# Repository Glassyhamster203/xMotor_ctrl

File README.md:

# xMotor_ctrl 

## An esp32 project

Project for HFUT RoboMaster team intramural competitions

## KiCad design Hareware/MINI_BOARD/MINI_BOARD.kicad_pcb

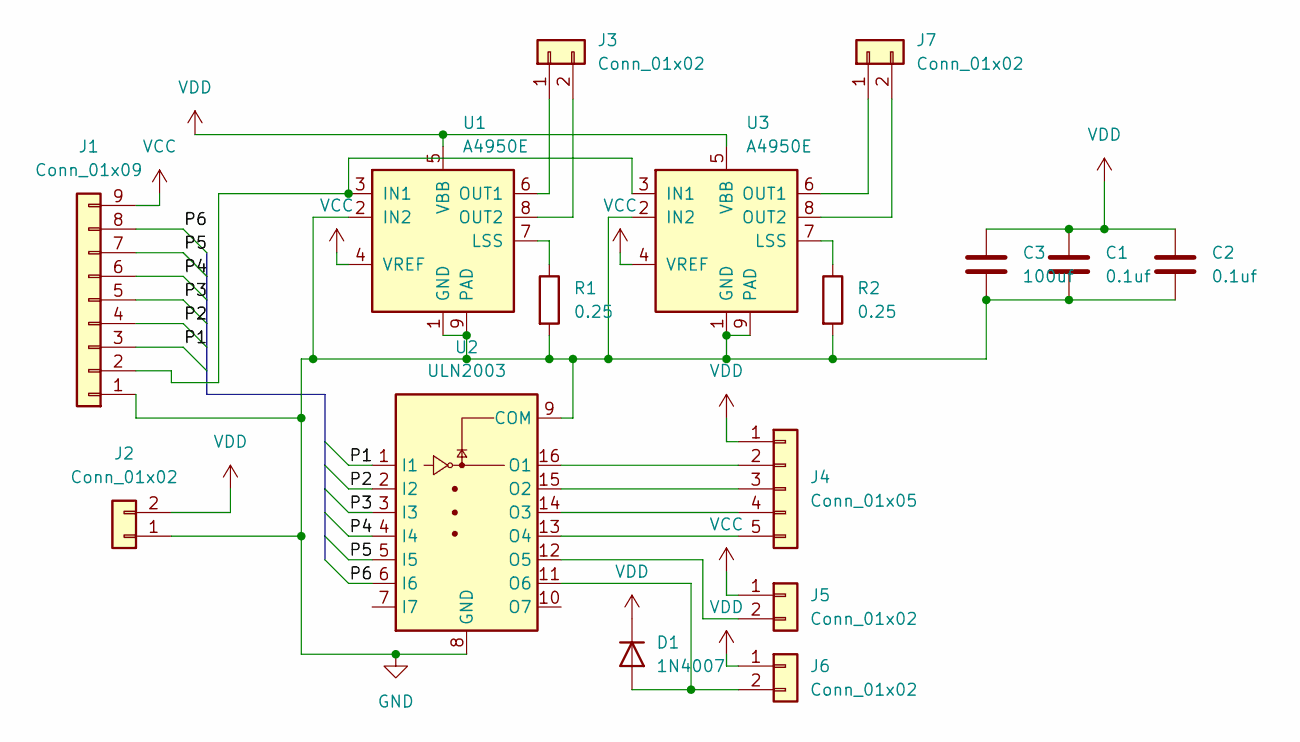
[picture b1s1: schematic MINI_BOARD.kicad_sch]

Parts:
C1, C2: 0.1uf; C_0603_1608Metric
C3: 100uf; CP_Radial_Tantal_D6.0mm_P5.00mm
D1: 1N4007; D_DO-41_SOD81_P10.16mm_Horizontal
J1: Conn_01x09; Wuerth_WR-WTB_64800911622_1x09_P1.50mm_Vertical
J2, J3, J6, J7: Conn_01x02; PhoenixContact_MCV_1,5_2-G-3.81_1x02_P3.81mm_Vertical
J4: Conn_01x05; PinHeader_1x05_P2.54mm_Vertical
J5: Conn_01x02; PinHeader_1x02_P2.54mm_Vertical
R1: 0.25; R_2512_6332Metric_Pad1.40x3.35mm_HandSolder
R2: 0.25; R_2816_7142Metric_Pad3.20x4.45mm_HandSolder
U1, U3: A4950E; SOIC-8-1EP_3.9x4.9mm_P1.27mm_EP2.41x3.3mm
U2: ULN2003; SOP-16_3.9x9.9mm_P1.27mm

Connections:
/P1: J1.3, U2.1 (I1)
/P2: J1.4, U2.2 (I2)
/P3: J1.5, U2.3 (I3)
/P4: J1.6, U2.4 (I4)
/P5: J1.7, U2.5 (I5)
/P6: J1.8, U2.6 (I6)
GND: C1.2, C2.2, C3.2, J1.1, J2.1, R1.2, R2.2, U1.1 (GND), U1.2 (IN2), U1.9 (PAD), U2.8 (GND), U2.9 (COM), U3.1 (GND), U3.2 (IN2), U3.9 (PAD)
unnamed: D1.2 (A), J6.2, U2.11 (O6)
unnamed: J1.2, U1.3 (IN1), U3.3 (IN1)
unnamed: J3.1, U1.6 (OUT1)
unnamed: J3.2, U1.8 (OUT2)
unnamed: J4.2, U2.16 (O1)
unnamed: J4.3, U2.15 (O2)
unnamed: J4.4, U2.14 (O3)
unnamed: J4.5, U2.13 (O4)
unnamed: J5.2, U2.12 (O5)
unnamed: J7.1, U3.6 (OUT1)
unnamed: J7.2, U3.8 (OUT2)
unnamed: R1.1, U1.7 (LSS)
unnamed: R2.1, U3.7 (LSS)
VCC: J1.9, J5.1, U1.4 (VREF), U3.4 (VREF)
VDD: C1.1, C2.1, C3.1, D1.1 (K), J2.2, J4.1, J6.1, U1.5 (VBB), U3.5 (VBB)

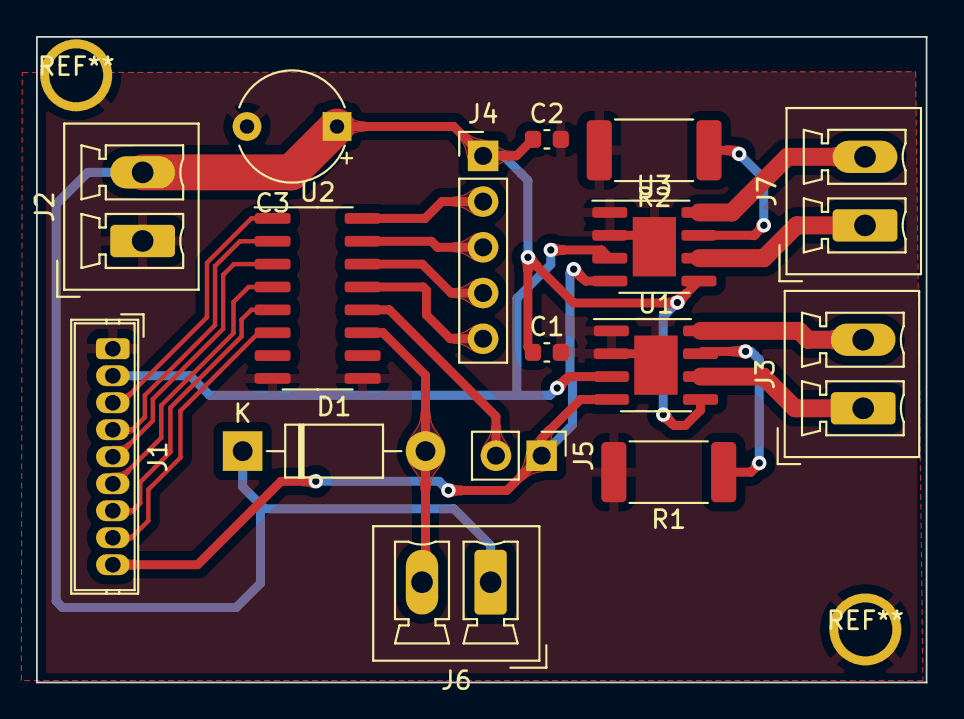
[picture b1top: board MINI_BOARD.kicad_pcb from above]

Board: 2 copper layers, 49.4 x 35.9 mm, 16 parts (0 on the bottom side), 22 nets.

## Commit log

2022-11-21 Add hardware firmware software
2022-11-23 change esp32
2022-11-23 Add STM32 project
2022-12-05 Add second board
